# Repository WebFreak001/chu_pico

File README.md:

# Chu Pico Large - Chunithm Style Controller

This is a fork of whowechina's [Chu Pico](https://github.com/whowechina/chu_pico) project, which is a half-sized DIY controller for chunithm-style games.

**CURRENTLY IN DEVELOPMENT, BOARD HARDWARE NOT YET TESTED!**

Differences from upstream:

* 500x100 mm board with 460x82 touch (key) area instead of 233x52 touch area
* replaced capacitive touch sensors with SMD variants, put them all on back panel
* added a 4th capacitive touch sensor (4 keys = 8 regions each)
* added connections for IR towers on left and right side (simple soldering pads)

For more information, see https://github.com/whowechina/chu_pico

## Part List

* Go JLCPCB and make order with the gerber zip files, regular FR-4 board, thickness is **1.6mm**
  * latest `Production\PCB\chu_main_xxx_large_yyy.zip`
  * latest `Production\PCB\chu_air_xxx.zip`

### Main

* 1x Rasberry Pico Pi Pico or Pico W.  
  https://www.raspberrypi.com/products/raspberry-pi-pico
  Becareful of 3 pins that are at the other side, they're difficult to solder and may leave air bubbles.  

* 1x USB Type-C socket (918-418K2023S40001 or KH-TYPE-C-16P)
* 36x WS2812B-4020 side-facing RGB LEDs.  
  https://www.lcsc.com/product-detail/Light-Emitting-Diodes-LED_Worldsemi-WS2812B-4020_C965557.html
* 1x TCA9548APWR (TSSOP-24) I2C multiplexer.  
  https://www.lcsc.com/product-detail/Signal-Switches-Encoders-Decoders-Multiplexers_Texas-Instruments-TCA9548APWR_C130026.html
* 4x MPR121 capacitive touch modules
* 5x Sharp GP2Y0E03 or ST VL53L0X ToF sensor modules, you need cables as well. Please note that the pictures are taken from upstream and depict the small controller.  
  https://www.lcsc.com/product-detail/Angle-Linear-Position-Sensors_Sharp-Microelectronics-GP2Y0E03_C920270.html  

   You can use both of them in a same PCB, the firmware will identify each of them automatically.  
  
* 4x 0603 75kohm resistors (R14, R15, R16, R17; one next to each MPR121 module on backside)
* 2x 0603 5.1kohm resistors (R1, R2; next to USB port).
* 10x 0603 4.7kohm resistors (all the remaining resistors - value from schematic, upstream project calls for 5.1kohm in their README, so perhaps try these instead).
* 12x 0603 1uF (0.1~1uF all fine) capacitors (C1 to C12)
* 3x Panasonic EVQP46B3M tiny tactile switches.  
  https://industry.panasonic.com/global/en/products/control/switch/light-touch/number/evqp46b3m

### Air Tower

* 3x PT333-3B photo transistor (Q2, Q4, Q6)
* 3x IR333C-A infrared LED emitters (D1, D2, D3)
* 3x 2N7002 MOSFETs (60V 115mA 1.7Ω@5V,50mA 200mW 2.5V 1 N-channel SOT-23) OR AO3400A (unclear from schematic) (Q1, Q3, Q5)
* 2x 47uF D5xL5.4mm polarized capacitors (I picked RVT1A470M0505 47UF 10V, but don't know if this was right yet) (C1, C2)
* 3x 0603 1ohm resistors (R2, R4, R6)
* 3x 0603 10ohm resistors (R1, R3, R5)
* 3x 0603 2kohm resistors (R7, R8, R9)
* 1x 0603 10kohm resistors (R10)

### Light Guide Panel

I have not yet cut any light panel, but the raw cut plan for it is inside [`PCB/main/3dmodels/keypad_kicad.svg`](PCB/main/3dmodels/keypad_kicad.svg) (dimensions: 481x93 mm)

### Case

No case available yet, see PCB file for exact mounting hole positions

WIP case blender file in [Production/CAD/case_large.blend](Production/CAD/case_large.blend)

## Firmware

The firmware is not yet adjusted to the large version, but should work with the following changes:
- adjust key layout (MPR121 at address 0x5A has keys K1-K8, 0x5B has keys K9-K16, 0x5C has keys K17-K24, 0x5D has keys K25-K32)
- enable IR towers by default (optional)

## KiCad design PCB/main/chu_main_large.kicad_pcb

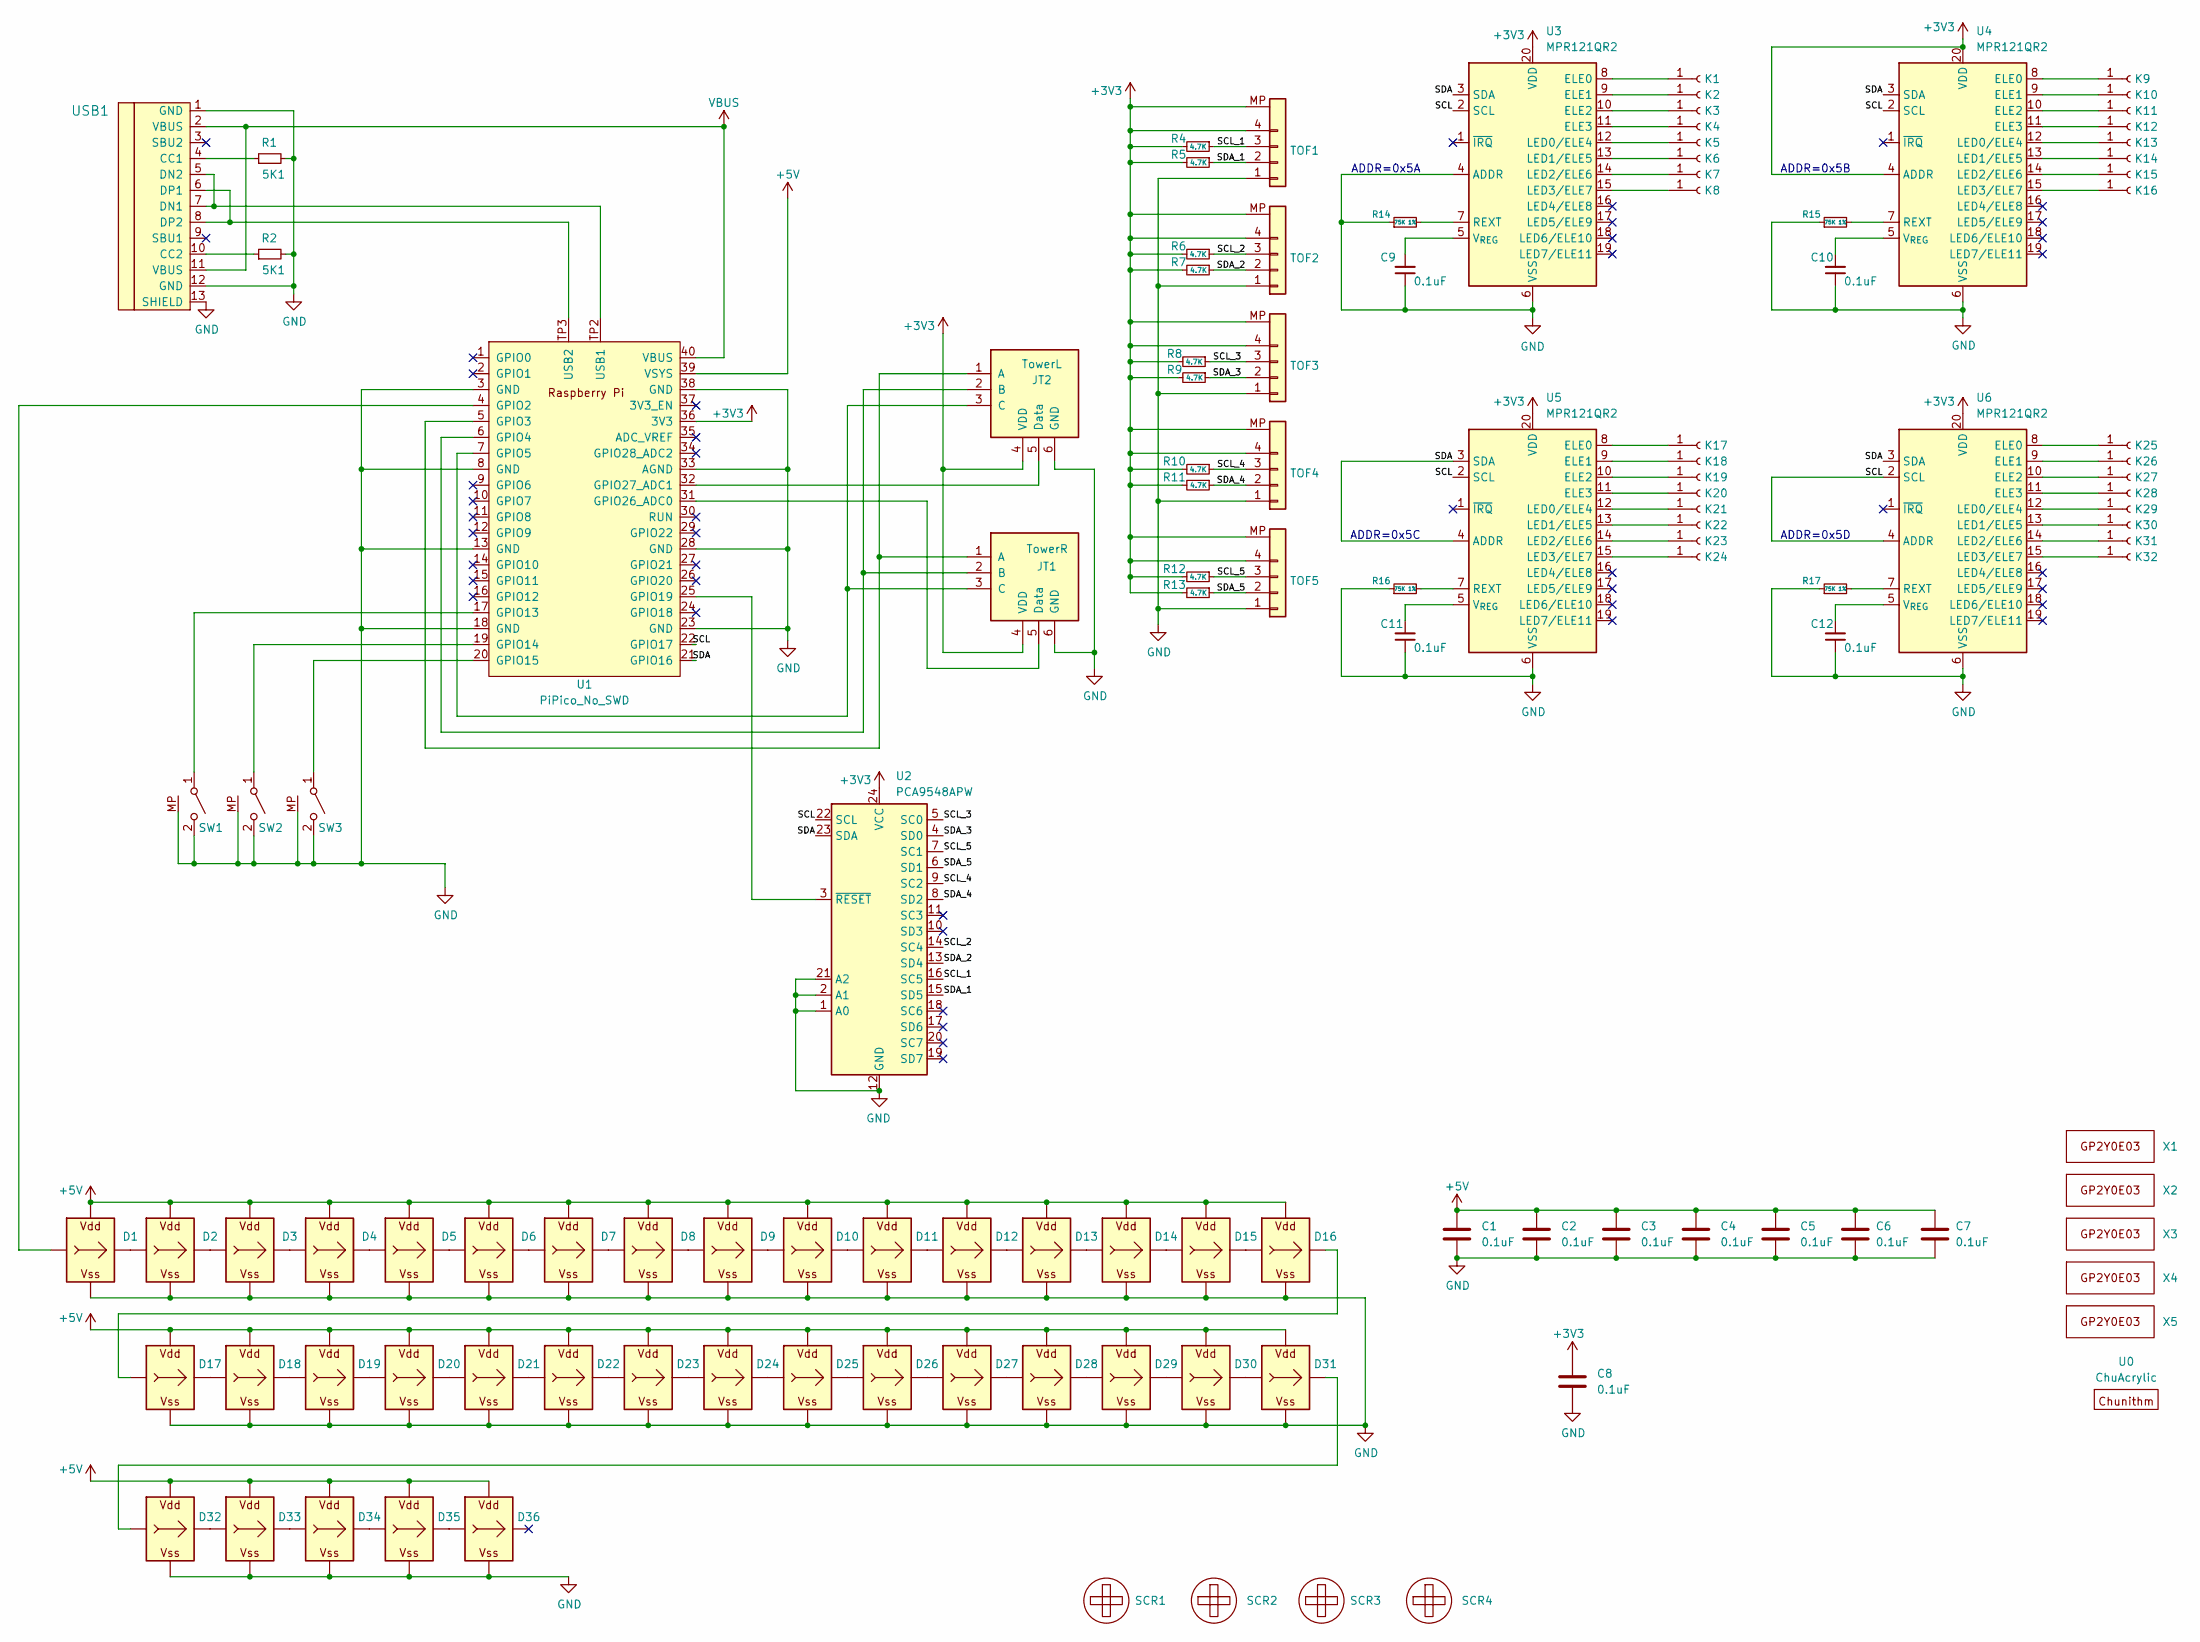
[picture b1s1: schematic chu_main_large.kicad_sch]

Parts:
C1, C2, C3, C4, C5, C6, C7, C8, C9, C10, C11, C12: 0.1uF; C_0603_1608Metric_Pad1.08x0.95mm_HandSolder
D1, D2, D3, D4, D5, D6, D7, D8, D9, D10, D11, D12, D13, D14, D15, D16, D17, D18, D19, D20, D21, D22, D23, D24, D25, D26, D27, D28, D29, D30, D31, D32, D33, D34, D35, D36: WS2812B_Unified; WS2812B-4020
JT1: TowerR; TowerConnector
JT2: TowerL; TowerConnector
K1: ChuKeyLarge
K2, K3, K4, K5, K6, K7, K8, K9, K10, K11, K12, K13, K14, K15, K16, K17, K18, K19, K20, K21, K22, K23, K24, K25, K26, K27, K28, K29, K30, K31, K32: Conn_01x01_Female; ChuKeyLarge
R1, R2: 5K1; R_0603_1608Metric_Pad0.98x0.95mm_HandSolder; LCSC C23186
R4, R5, R6, R7, R8, R9, R10, R11, R12, R13: 4.7K; R_0603_1608Metric_Pad0.98x0.95mm_HandSolder; LCSC C23186
R14, R15, R16, R17: 75K 1%; R_0603_1608Metric_Pad0.98x0.95mm_HandSolder
SCR1, SCR2, SCR3, SCR4: ScrewHole; MountingHole_3.2mm_M3
SW1, SW2, SW3: SPST_EVQP4; SW_EVQ-P46B3M
TOF1, TOF2, TOF3, TOF4, TOF5: TOF_I2C; SH1.0_4P_Solder_Combo
U0: ChuAcrylic; ChuAcrylicLarge
U1: PiPico_No_SWD; RPi_Pico_SMD_Pins_No_SWD
U2: PCA9548APW; TSSOP-24_4.4x7.8mm_P0.65mm
U3, U4, U5, U6: MPR121QR2; UQFN-20_3x3mm_P0.4mm
USB1: U262-161N-4BVC11; HRO-TYPE-C-31-M-12-Assembly; LCSC C319148
X1, X2, X3, X4, X5: GP2Y0E03_REAL

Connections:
+3V3: C8.1, JT1.4 (VDD), JT2.4 (VDD), R4.2, R5.2, R6.2, R7.2, R8.2, R9.2, R10.2, R11.2, R12.2, R13.2, TOF1.4, TOF1.MP, TOF2.4, TOF2.MP, TOF3.4, TOF3.MP, TOF4.4, TOF4.MP, TOF5.4, TOF5.MP, U1.36 (3V3), U2.24 (VCC), U3.20 (VDD), U4.4 (ADDR), U4.20 (VDD), U5.20 (VDD), U6.20 (VDD)
+5V: C1.1, C2.1, C3.1, C4.1, C5.1, C6.1, C7.1, D1.V (VDD), D2.V (VDD), D3.V (VDD), D4.V (VDD), D5.V (VDD), D6.V (VDD), D7.V (VDD), D8.V (VDD), D9.V (VDD), D10.V (VDD), D11.V (VDD), D12.V (VDD), D13.V (VDD), D14.V (VDD), D15.V (VDD), D16.V (VDD), D17.V (VDD), D18.V (VDD), D19.V (VDD), D20.V (VDD), D21.V (VDD), D22.V (VDD), D23.V (VDD), D24.V (VDD), D25.V (VDD), D26.V (VDD), D27.V (VDD), D28.V (VDD), D29.V (VDD), D30.V (VDD), D31.V (VDD), D32.V (VDD), D33.V (VDD), D34.V (VDD), D35.V (VDD), D36.V (VDD), U1.39 (VSYS)
/SCL: U1.22 (GPIO17), U2.22 (SCL), U3.2 (SCL), U4.2 (SCL), U5.2 (SCL), U6.2 (SCL), U6.4 (ADDR)
/SCL_1: R4.1, TOF1.3, U2.16 (SC5)
/SCL_2: R6.1, TOF2.3, U2.14 (SC4)
/SCL_3: R8.1, TOF3.3, U2.5 (SC0)
/SCL_4: R10.1, TOF4.3, U2.9 (SC2)
/SCL_5: R12.1, TOF5.3, U2.7 (SC1)
/SDA: U1.21 (GPIO16), U2.23 (SDA), U3.3 (SDA), U4.3 (SDA), U5.3 (SDA), U5.4 (ADDR), U6.3 (SDA)
/SDA_1: R5.1, TOF1.2, U2.15 (SD5)
/SDA_2: R7.1, TOF2.2, U2.13 (SD4)
/SDA_3: R9.1, TOF3.2, U2.4 (SD0)
/SDA_4: R11.1, TOF4.2, U2.8 (SD2)
/SDA_5: R13.1, TOF5.2, U2.6 (SD1)
GND: C1.2, C2.2, C3.2, C4.2, C5.2, C6.2, C7.2, C8.2, C9.1, C10.1, C11.1, C12.1, D1.G (VSS), D2.G (VSS), D3.G (VSS), D4.G (VSS), D5.G (VSS), D6.G (VSS), D7.G (VSS), D8.G (VSS), D9.G (VSS), D10.G (VSS), D11.G (VSS), D12.G (VSS), D13.G (VSS), D14.G (VSS), D15.G (VSS), D16.G (VSS), D17.G (VSS), D18.G (VSS), D19.G (VSS), D20.G (VSS), D21.G (VSS), D22.G (VSS), D23.G (VSS), D24.G (VSS), D25.G (VSS), D26.G (VSS), D27.G (VSS), D28.G (VSS), D29.G (VSS), D30.G (VSS), D31.G (VSS), D32.G (VSS), D33.G (VSS), D34.G (VSS), D35.G (VSS), D36.G (VSS), JT1.6 (GND), JT2.6 (GND), R1.2, R2.2, R14.1, R15.1, R16.1, R17.1, SW1.2 (B), SW1.MP, SW2.2 (B), SW2.MP, SW3.2 (B), SW3.MP, TOF1.1, TOF2.1, TOF3.1, TOF4.1, TOF5.1, U1.3 (GND), U1.8 (GND), U1.13 (GND), U1.18 (GND), U1.23 (GND), U1.28 (GND), U1.33 (AGND), U1.38 (GND), U2.1 (A0), U2.2 (A1), U2.12 (GND), U2.21 (A2), U3.4 (ADDR), U3.6 (VSS), U4.6 (VSS), U5.6 (VSS), U6.6 (VSS), USB1.1 (GND), USB1.12 (GND), USB1.13 (SHIELD)
unnamed: D1.I (In), U1.4 (GPIO2)
unnamed: D1.O (Out), D2.I (In)
unnamed: D2.O (Out), D3.I (In)
unnamed: D3.O (Out), D4.I (In)
unnamed: D4.O (Out), D5.I (In)
unnamed: D5.O (Out), D6.I (In)
unnamed: D6.O (Out), D7.I (In)
unnamed: D7.O (Out), D8.I (In)
unnamed: D8.O (Out), D9.I (In)
unnamed: D9.O (Out), D10.I (In)
unnamed: D10.O (Out), D11.I (In)
unnamed: D11.O (Out), D12.I (In)
unnamed: D12.O (Out), D13.I (In)
unnamed: D13.O (Out), D14.I (In)
unnamed: D14.O (Out), D15.I (In)
unnamed: D15.O (Out), D16.I (In)
unnamed: D16.O (Out), D17.I (In)
unnamed: D17.O (Out), D18.I (In)
unnamed: D18.O (Out), D19.I (In)
unnamed: D19.O (Out), D20.I (In)
unnamed: D20.O (Out), D21.I (In)
unnamed: D21.O (Out), D22.I (In)
unnamed: D22.O (Out), D23.I (In)
unnamed: D23.O (Out), D24.I (In)
unnamed: D24.O (Out), D25.I (In)
unnamed: D25.O (Out), D26.I (In)
unnamed: D26.O (Out), D27.I (In)
unnamed: D27.O (Out), D28.I (In)
unnamed: D28.O (Out), D29.I (In)
unnamed: D29.O (Out), D30.I (In)
unnamed: D30.O (Out), D31.I (In)
unnamed: D31.O (Out), D32.I (In)
unnamed: D32.O (Out), D33.I (In)
unnamed: D33.O (Out), D34.I (In)
unnamed: D34.O (Out), D35.I (In)
unnamed: D35.O (Out), D36.I (In)
unnamed: JT1.1 (A), JT2.1 (A), U1.5 (GPIO3)
unnamed: JT1.2 (B), JT2.2 (B), U1.6 (GPIO4)
unnamed: JT1.3 (C), JT2.3 (C), U1.7 (GPIO5)
unnamed: JT1.5 (Data), U1.31 (GPIO26_ADC0)
unnamed: JT2.5 (Data), U1.32 (GPIO27_ADC1)
unnamed: K1.1, U3.8 (ELE0)
unnamed: K2.1, U3.9 (ELE1)
unnamed: K3.1, U3.10 (ELE2)
unnamed: K4.1, U3.11 (ELE3)
unnamed: K5.1, U3.12 (LED0/ELE4)
unnamed: K6.1, U3.13 (LED1/ELE5)
unnamed: K7.1, U3.14 (LED2/ELE6)
unnamed: K8.1, U3.15 (LED3/ELE7)
unnamed: K9.1, U4.8 (ELE0)
unnamed: K10.1, U4.9 (ELE1)
unnamed: K11.1, U4.10 (ELE2)
unnamed: K12.1, U4.11 (ELE3)
unnamed: K13.1, U4.12 (LED0/ELE4)
unnamed: K14.1, U4.13 (LED1/ELE5)
unnamed: K15.1, U4.14 (LED2/ELE6)
unnamed: K16.1, U4.15 (LED3/ELE7)
unnamed: K17.1, U5.8 (ELE0)
unnamed: K18.1, U5.9 (ELE1)
unnamed: K19.1, U5.10 (ELE2)
unnamed: K20.1, U5.11 (ELE3)
unnamed: K21.1, U5.12 (LED0/ELE4)
unnamed: K22.1, U5.13 (LED1/ELE5)
unnamed: K23.1, U5.14 (LED2/ELE6)
unnamed: K24.1, U5.15 (LED3/ELE7)
unnamed: K25.1, U6.8 (ELE0)
unnamed: K26.1, U6.9 (ELE1)
unnamed: K27.1, U6.10 (ELE2)
unnamed: K28.1, U6.11 (ELE3)
unnamed: K29.1, U6.12 (LED0/ELE4)
unnamed: K30.1, U6.13 (LED1/ELE5)
unnamed: K31.1, U6.14 (LED2/ELE6)
unnamed: K32.1, U6.15 (LED3/ELE7)
unnamed: SW1.1 (A), U1.17 (GPIO13)
unnamed: SW2.1 (A), U1.19 (GPIO14)
unnamed: SW3.1 (A), U1.20 (GPIO15)
unnamed: U1.25 (GPIO19), U2.3 (~RESET)
unnamed: U1.TP2 (USB1), USB1.5 (DN2), USB1.7 (DN1)
unnamed: U1.TP3 (USB2), USB1.6 (DP1), USB1.8 (DP2)
unnamed: R14.2, U3.7 (REXT)
unnamed: C9.2, U3.5 (V_{REG})
unnamed: R15.2, U4.7 (REXT)
unnamed: C10.2, U4.5 (V_{REG})
unnamed: R16.2, U5.7 (REXT)
unnamed: C11.2, U5.5 (V_{REG})
unnamed: R17.2, U6.7 (REXT)
unnamed: C12.2, U6.5 (V_{REG})
unnamed: R1.1, USB1.4 (CC1)
unnamed: R2.1, USB1.10 (CC2)
VBUS: U1.40 (VBUS), USB1.2 (VBUS), USB1.11 (VBUS)

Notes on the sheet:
ADDR=0x5C
ADDR=0x5D
ADDR=0x5A
ADDR=0x5B

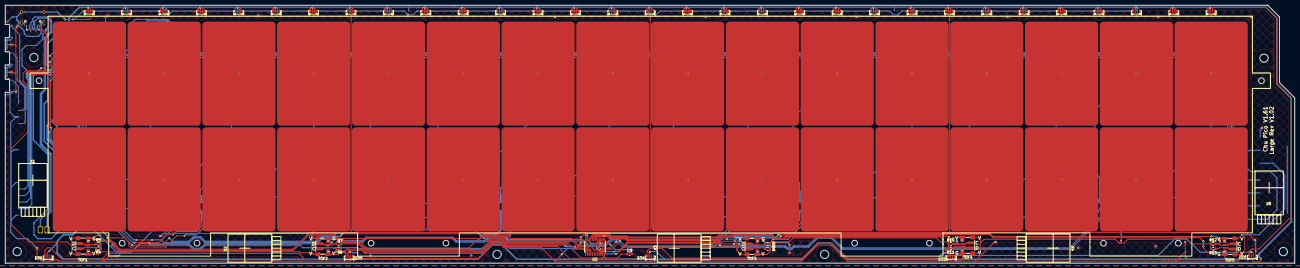
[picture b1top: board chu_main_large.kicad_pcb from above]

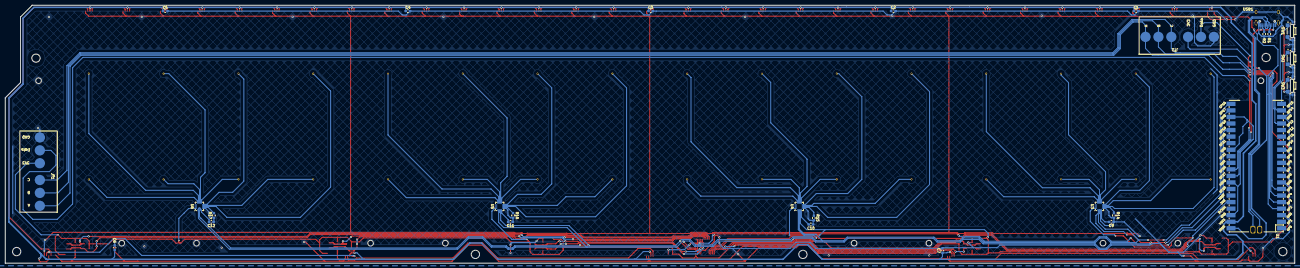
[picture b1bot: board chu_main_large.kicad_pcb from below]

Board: 2 copper layers, 500.0 x 100.0 mm, 125 parts (28 on the bottom side), 105 nets.

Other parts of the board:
SCR4#2, SCR4#3: ScrewHole; MountingHole_3.2mm_M3

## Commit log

2025-05-19 initial fork version
2025-05-19 improve touch based on online infos
2025-05-21 solder improvements, started case
2025-05-23 update zip
2025-05-25 update parts in readme for tower
2025-06-12 fix LED orientation
